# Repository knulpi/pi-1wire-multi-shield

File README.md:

<h1 align="center">
1-wire multi-shield for Raspberry Pi
</h1>

> Use up to six 1-wire bus lines to connect multiple sensors on long lines.

<div align="center">
    
</div>

_[🇩🇪 Deutsche version](LIESMICH.md)_

This is a project providing a circuit and PCB design for a Raspberry Pi shield. 
The board can connect up to six 1-wire buses, enabling to connect up to around 60 sensors, such as the DS18B20.
Each data pin of the terminals is wired to one specific GPIO.
The board can easily be plugged onto a Raspberry Pi.

## Motivation

Connecting 1-wire sensors with long lines is error-prone and will not work with many sensors.
You may get random disappearing sensors or bad value readings.
Splitting problematic sensor lines into own buses greatly reduces these inabilities.

## Circuit

The circuit is quite simple. It basically connects 
- the GND terminals with a Raspberry GND pin
- the VDD terminals with the Raspberry's 5V net
- each Data terminal pin with an own GPIO
- used data pins are
  - GPIO 4, 5, 6, 17, 22, 27

Since the Raspberry's data pins operate at 3V3, the pull-up resistors for the data lines are using
the 3V3 net of the Raspberry.
The pull-ups are lower than the default recommended value (4k7). 
This should stabilize long bus lines.

Each power net has a 47uF capacitor for stabilization.

## PCB

The PCB follows the schematic. 
The pin-header is mounted on the bottom side of the board (see images).
This enables the board to be connected directly with the Raspberry pin headers.

Each screw terminal is connected to one net. There is one for GND, one for VDD and one for DATA.
Be aware that you might reduce more insulation of your cables to reach all terminals.

## Parts

The gerber files can be used to directly order the board, e.g. via [Aisler](https://aisler.net/p/NHLBOVQZ).

The following parts are needed:
- 6x 2k7 resistors or similar
- 2x 47µF capacitors or similar
- Pitch Screw Terminal Blocks with a 5.08mm pin distance to connect 3x6 wires (e.g. 3x6-pin-blocks or 6x3-pin-blocks etc.)
- A 20x2 pin female header with a 2.54mm pin distance

## Software

> ⚠ Your kernel must not be too old, so that it supports multiple 1-wire enabled GPIOs 

To set up your Pi, enable each GPIO used for 1-wire protocol in your `/boot/config.txt`. 
Every GPIO we connected will have its own line. 
If you are unsure what to do, follow other tutorials in the web that describe the procedure in detail, 
like [this tutorial](https://blog.oddbit.com/post/2018-03-27-multiple-1-wire-buses-on-the/).

In the end, your `/boot/config.txt` file should contain these lines:
```
dtoverlay=w1-gpio,gpiopin=4
dtoverlay=w1-gpio,gpiopin=5
dtoverlay=w1-gpio,gpiopin=6
dtoverlay=w1-gpio,gpiopin=17
dtoverlay=w1-gpio,gpiopin=22
dtoverlay=w1-gpio,gpiopin=27
```

Restart and your sensors will appear in `/sys/bus/w1/devices`.

## General recommendations
- use shielded wires on long connections
- lower the resistor to something like 1k5 if you are getting problems with many sensors

## Contributing

Feel free to open Pull Requests or just create issues if you feel that something is missing or can be improved.

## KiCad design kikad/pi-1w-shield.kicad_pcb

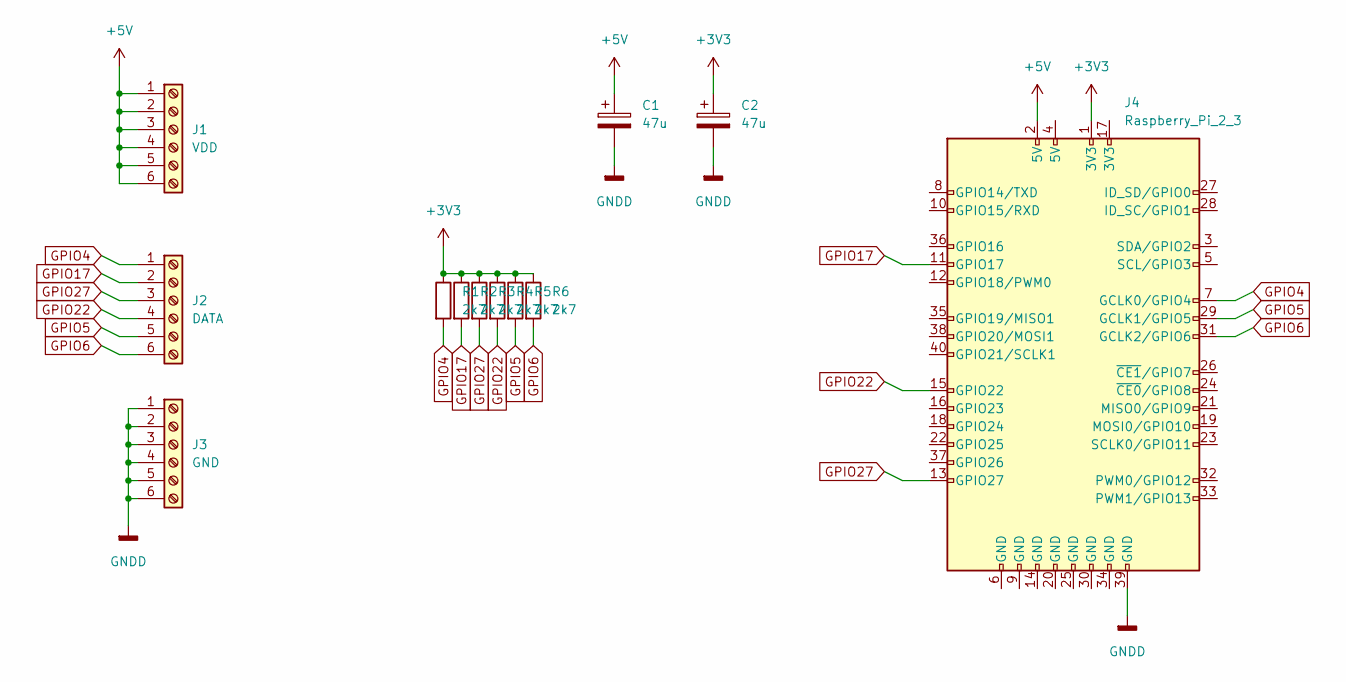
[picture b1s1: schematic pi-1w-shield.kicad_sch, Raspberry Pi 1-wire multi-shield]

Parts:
C1, C2: 47u; CP_Radial_D6.3mm_P2.50mm
J1: VDD; TerminalBlock_Phoenix_MKDS-1,5-6-5.08_1x06_P5.08mm_Horizont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
J2: DATA; TerminalBlock_Phoenix_MKDS-1,5-6-5.08_1x06_P5.08mm_Horizont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
J3: GND; TerminalBlock_Phoenix_MKDS-1,5-6-5.08_1x06_P5.08mm_Horizont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
J4: Raspberry_Pi_2_3; PinSocket_2x20_P2.54mm_Vertical
R1, R2, R3, R4, R5, R6: 2k7; R_Axial_DIN0207_L6.3mm_D2.5mm_P10.16mm_Horizontal

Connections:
+3V3: C2.1, J4.1 (3V3), R1.1, R2.1, R3.1, R4.1, R5.1, R6.1
+5V: C1.1, J1.1, J1.2, J1.3, J1.4, J1.5, J1.6, J4.2 (5V)
GNDD: C1.2, C2.2, J3.1, J3.2, J3.3, J3.4, J3.5, J3.6, J4.39 (GND)
GPIO4: J2.1, J4.7 (GCLK0/GPIO4), R1.2
GPIO5: J2.5, J4.29 (GCLK1/GPIO5), R5.2
GPIO6: J2.6, J4.31 (GCLK2/GPIO6), R6.2
GPIO17: J2.2, J4.11 (GPIO17), R2.2
GPIO22: J2.4, J4.15 (GPIO22), R4.2
GPIO27: J2.3, J4.13 (GPIO27), R3.2

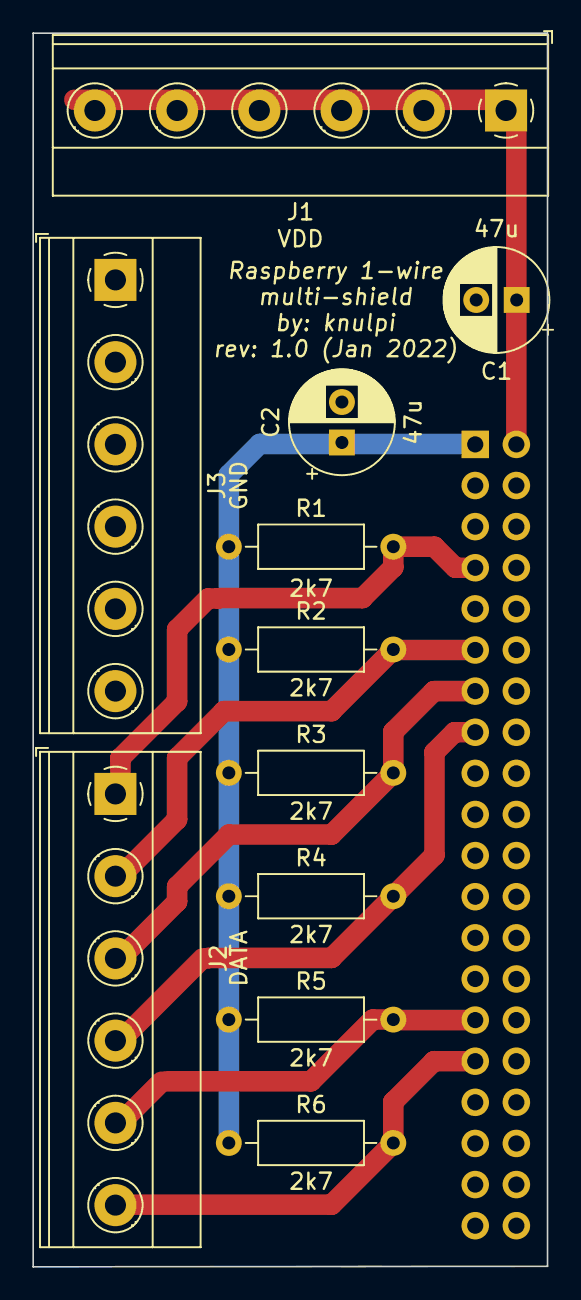
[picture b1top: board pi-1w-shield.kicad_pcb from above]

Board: 2 copper layers, 31.8 x 76.2 mm, 12 parts (1 on the bottom side), 9 nets.

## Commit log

2022-01-13 add gerber files
2022-01-13 add README.md and images
2022-01-13 move headline up
2022-01-13 fix typo
2022-01-13 add LIESMICH.md
2023-12-06 Fix typos
2023-12-07 Create LICENSE
